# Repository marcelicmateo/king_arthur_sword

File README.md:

# King Arthur's sword

Shenanigans with pulling sword out of stone. Only the chosen one['s] are fit to be a king.
# Release
This is release present in real life system. Depoyed solution. 
# Project

As a part of sword exibition, we made artifitial stone to hold a sword. Sword was locked in stone by mechanism, and by random chance, relesased. 
Participant of exibition could then try and pull the sword out of stone, if GOD of random was on their side, they would then become Kings. 

# Setup 

```
https://github.com/marcelicmateo/king_arthur_sword 
```
Run platformio and compile. 

## Hardware

This was builded and tested on Espressif, ESP8266 based dev board, [Nodemcu v1](https://www.nodemcu.com/index_en.html#fr_54747661d775ef1a3600009e).

# Details

Project details and development decisions are described on WIKI.

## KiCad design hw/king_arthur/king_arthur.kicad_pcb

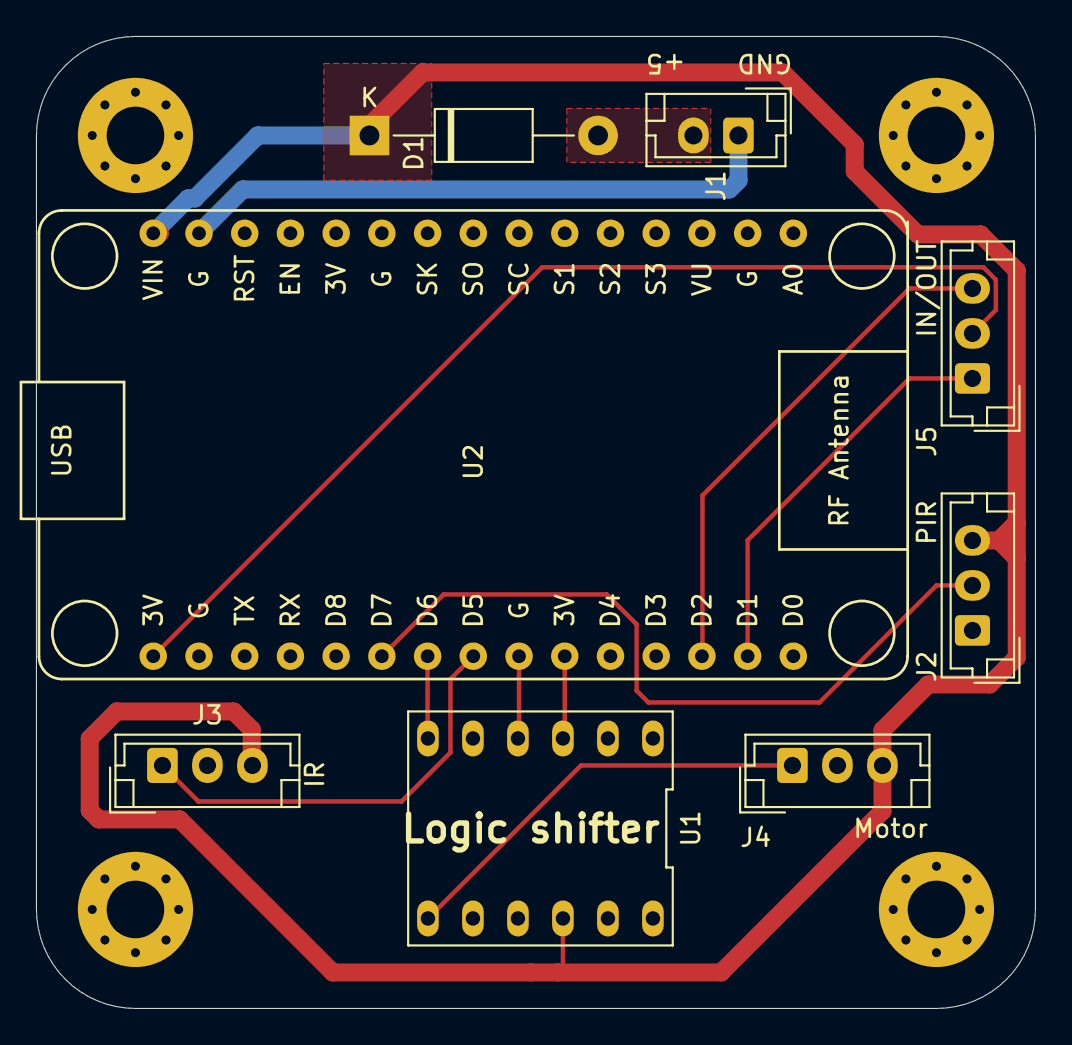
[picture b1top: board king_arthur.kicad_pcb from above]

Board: 2 copper layers, 55.5 x 54.0 mm, 12 parts (0 on the bottom side), 11 nets.

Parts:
D1: D; D_DO-41_SOD81_P12.70mm_Horizontal
H1, H2, H3, H4: MountingHole_Pad; MountingHole_3.2mm_M3_Pad_Via
J1: POWER; JST_EH_B2B-EH-A_1x02_P2.50mm_Vertical
J2: PIR sensor; JST_EH_B3B-EH-A_1x03_P2.50mm_Vertical
J3: IR sensor; JST_EH_B3B-EH-A_1x03_P2.50mm_Vertical
J4: Servo motor; JST_EH_B3B-EH-A_1x03_P2.50mm_Vertical
J5: Motor state - unlock/lock; JST_EH_B3B-EH-A_1x03_P2.50mm_Vertical
U1: Logisshifter; DIP-12_393_ELL
U2: NodeMCU_1.0_(ESP-12E); ESP12F-Devkit-V3

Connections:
+3V3: J5.2, U2.16
+5V: D1.1, J2.3, J3.3, J4.3, U1.10, U2.15
GND: H1.1, H2.1, H3.1, H4.1, J1.1, J2.1, J3.2, J4.2, U1.4, U1.9, U2.14, U2.24
IR: J3.1, U2.23
Motor: J4.1, U1.7
unnamed: D1.2, J1.2
unnamed: U1.3, U2.25
unnamed: U1.6, U2.22
PIN_IN: J5.3, U2.28
PIN_OUT: J5.1, U2.29
PIR: J2.2, U2.21

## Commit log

2021-03-01 First commit, v1
2021-03-04 new MCU
2021-03-08 linted
2021-03-08 pot for probability
2021-03-09 fix probability bug,
2021-03-09 some mesage
2021-03-17 server setup in progress
2021-03-18 INCLUDE . h and flow diagram programed
2021-03-18 lock and unlock logic
2021-03-18 clean includes
2021-03-20 web page update function
2021-03-21 mijenjanje postotka prolaznosti
2021-03-21 few style changes
2021-03-21 dash.h removed
2021-03-25 added motor control with sensors
2021-03-25 update schematik
2021-03-25 cad changes
2021-03-25 removed tests
2021-03-25 fix blockig while loop
2021-03-26 ver1 cad
2021-03-26 save
2021-03-28 bug fix
2021-03-29 new flow plus control
2021-03-30 ver 2, deploy push 1.0
2021-04-01 coments deletion
2021-04-02 code clean up
2021-04-02 add error functions and states
2021-04-03 gpio header file
2021-04-03 finaly web page is more responisve
2021-04-05 -Ofast added
2021-04-05 error handling and reporting done
2021-04-05 more main clean up
2021-04-07 add read write to file functions
2021-04-07 celan up of bngo code
2021-04-07 genrate winners function added
2021-04-07 generate new bingo
2021-04-07 paly bingo logic
2021-04-07 default var updated
2021-04-07 debug print state
2021-04-07 estetics changes
2021-04-08 chane current player is fixed
2021-04-11 current player update on dashboard
2021-04-11 clean up
2021-04-11 clean
2021-04-11 clean CAD
2021-04-11 shematic and pcb done
2021-04-12 Ver 1.
2021-04-12 read me update
2021-04-12 export pcb, schema and stl files
2021-04-20 production
2021-05-09 update debug
2021-05-10 true random
2021-05-14 ispravak
2021-05-15 last push to main
2021-05-15 state changes and error handling rewrite
2021-05-15 reporting to web fixerd
2021-05-15 serial debug and relese
2021-05-15 get more speed
2021-05-17 release vesion 3: final
2021-05-17 Final release
2021-05-23 rpi and piton
